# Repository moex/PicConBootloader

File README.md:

PicConBootloader
================

Primeras placas de Pic con Bootloader

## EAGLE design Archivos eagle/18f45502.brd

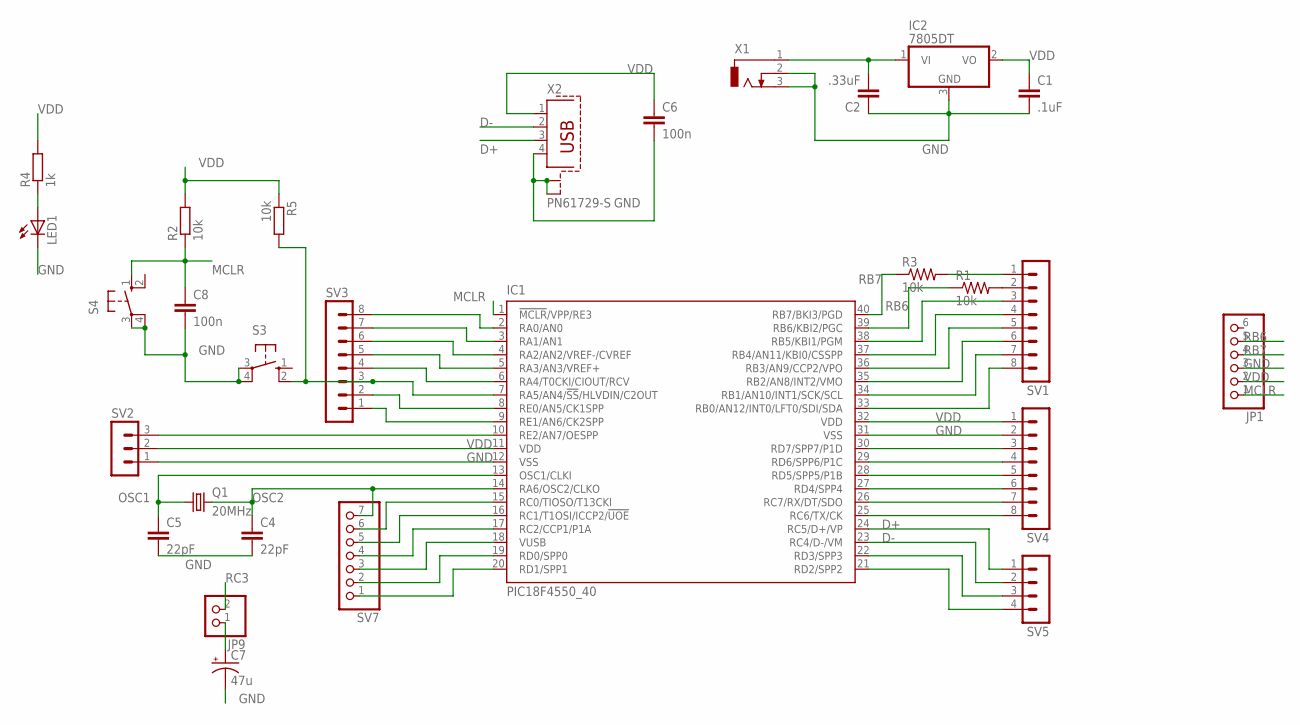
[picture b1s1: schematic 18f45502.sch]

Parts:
C1: .1uF; C0805K
C2: .33uF; C0805K
C4, C5: 22pF; C0805K
C6, C8: 100n; C0805K
C7: 47u; TT2D5L
IC1: PIC18F4550_40; DIL40
IC2: 7805DT; TO252
JP1: PINHD-1X6; 1X06
JP9: PINHD-1X2; 1X02
LED1: LED3MM
Q1: 20MHz; HC49/S
R1, R2, R3, R5: 10k; R0805
R4: 1k; R0805
S3, S4: 10-XX; B3F-10XX
SV1, SV3, SV4: MA08-1
SV2: MA03-1
SV5: MA04-1
SV7: PINHD-1X7; 1X07
X1: DCJ0202
X2: PN61729-S

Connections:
D+: IC1.24 (RC5/D+/VP), SV5.1, X2.3
D-: IC1.23 (RC4/D-/VM), SV5.2, X2.2
GND: C1.2, C2.1, C4.2, C5.2, C6.2, C7.-, C8.2, IC1.12 (VSS), IC1.31 (VSS), IC2.3 (GND), JP1.3, LED1.K (C), S3.3, S3.4 (P1), S4.3, S4.4 (P1), SV2.1, SV4.2, X1.2, X1.3, X2.4, X2.S1, X2.S2
MCLR: C8.1, IC1.1 (!MCLR!/VPP/RE3), JP1.1, R2.1, S4.1 (S)
unnamed: R3.2, SV1.1
unnamed: R1.2, SV1.2
unnamed: IC1.38 (RB5/KBI1/PGM), SV1.3
unnamed: IC1.37 (RB4/AN11/KBI0/CSSPP), SV1.4
unnamed: IC1.36 (RB3/AN9/CCP2/VPO), SV1.5
unnamed: IC1.35 (RB2/AN8/INT2/VMO), SV1.6
unnamed: IC1.34 (RB1/AN10/INT1/SCK/SCL), SV1.7
unnamed: IC1.33 (RB0/AN12/INT0/LFT0/SDI/SDA), SV1.8
unnamed: IC1.30 (RD7/SPP7/P1D), SV4.3
unnamed: IC1.29 (RD6/SPP6/P1C), SV4.4
unnamed: IC1.28 (RD5/SPP5/P1B), SV4.5
unnamed: IC1.27 (RD4/SPP4), SV4.6
unnamed: IC1.2 (RA0/AN0), SV3.8
unnamed: IC1.3 (RA1/AN1), SV3.7
unnamed: IC1.4 (RA2/AN2/VREF-/CVREF), SV3.6
unnamed: IC1.5 (RA3/AN3/VREF+), SV3.5
unnamed: IC1.6 (RA4/T0CKI/CIOUT/RCV), SV3.4
unnamed: IC1.7 (RA5/AN4/!SS!/HLVDIN/C2OUT), R5.2, S3.2 (S1), SV3.3
unnamed: IC1.10 (RE2/AN7/OESPP), SV2.3
unnamed: IC1.9 (RE1/AN6/CK2SPP), SV3.1
unnamed: IC1.8 (RE0/AN5/CK1SPP), SV3.2
unnamed: IC1.21 (RD2/SPP2), SV5.4
unnamed: IC1.22 (RD3/SPP3), SV5.3
unnamed: IC1.15 (RC0/TIOSO/T13CKI), SV7.6
unnamed: IC1.16 (RC1/T1OSI/ICCP2/!UOE), SV7.5
unnamed: IC1.17 (RC2/CCP1/P1A), SV7.4
unnamed: IC1.26 (RC7/RX/DT/SDO), SV4.7
unnamed: IC1.25 (RC6/TX/CK), SV4.8
unnamed: IC1.19 (RD0/SPP0), SV7.2
unnamed: IC1.20 (RD1/SPP1), SV7.1
unnamed: LED1.A, R4.1
unnamed: C2.2, IC2.1 (VI), X1.1
unnamed: C7.+, JP9.1
OSC1: C5.1, IC1.13 (OSC1/CLKI), Q1.1
OSC2: C4.1, IC1.14 (RA6/OSC2/CLKO), Q1.2, SV7.7
RB6: IC1.39 (RB6/KBI2/PGC), JP1.5, R1.1
RB7: IC1.40 (RB7/BKI3/PGD), JP1.4, R3.1
RC3: IC1.18 (VUSB), JP9.2, SV7.3
VDD: C1.1, C6.1, IC1.11 (VDD), IC1.32 (VDD), IC2.2 (VO), JP1.2, R2.2, R4.2, R5.1, SV2.2, SV4.1, X2.1

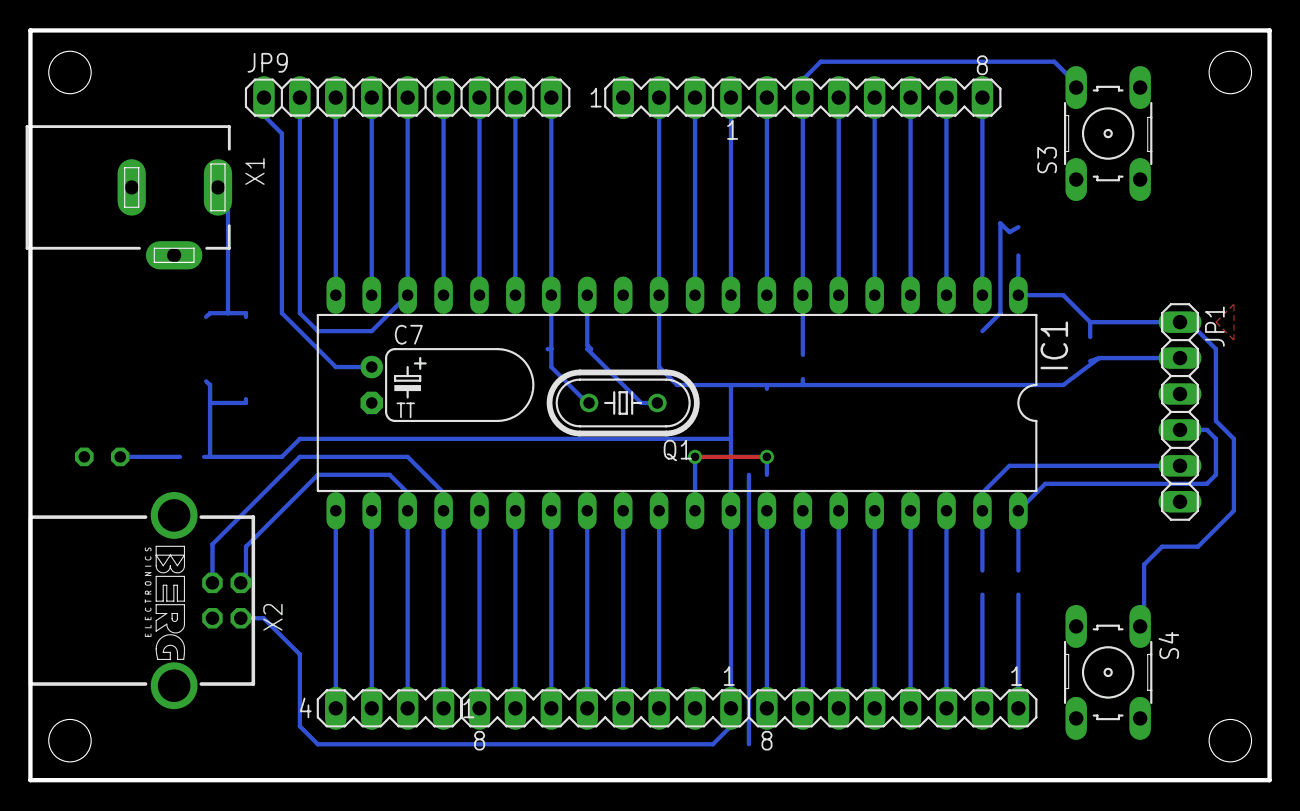
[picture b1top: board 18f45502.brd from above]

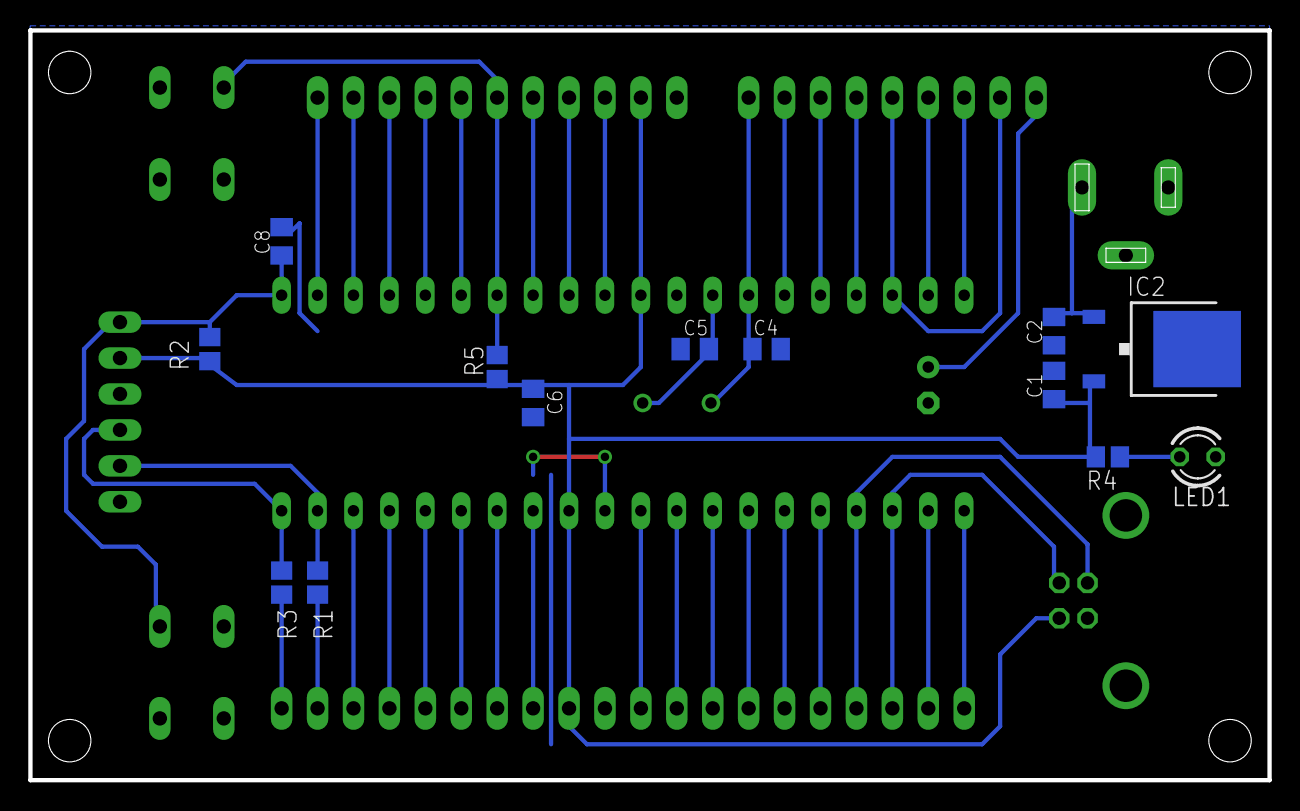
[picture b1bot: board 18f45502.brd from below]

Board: 2 copper layers, 87.6 x 53.0 mm, 28 parts (13 on the bottom side), 43 nets.

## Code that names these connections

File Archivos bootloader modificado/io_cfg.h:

/*********************************************************************
 *
 *                Microchip USB C18 Firmware 
 *
 *********************************************************************
 * FileName:        io_cfg.h
 * Dependencies:    See INCLUDES section below
 * Processor:       PIC18
 * Compiler:        C18 3.11+
 * Company:         Microchip Technology, Inc.
 *
 * Software License Agreement
 *
 * The software supplied herewith by Microchip Technology Incorporated
 * (the Company) for its PICmicro® Microcontroller is intended and
 * supplied to you, the Companys customer, for use solely and
 * exclusively on Microchip PICmicro Microcontroller products. The
 * software is owned by the Company and/or its supplier, and is
 * protected under applicable copyright laws. All rights are reserved.
 * Any use in violation of the foregoing restrictions may subject the
 * user to criminal sanctions under applicable laws, as well as to
 * civil liability for the breach of the terms and conditions of this
 * license.
 *
 * THIS SOFTWARE IS PROVIDED IN AN AS IS CONDITION. NO WARRANTIES,
 * WHETHER EXPRESS, IMPLIED OR STATUTORY, INCLUDING, BUT NOT LIMITED
 * TO, IMPLIED WARRANTIES OF MERCHANTABILITY AND FITNESS FOR A
 * PARTICULAR PURPOSE APPLY TO THIS SOFTWARE. THE COMPANY SHALL NOT,
 * IN ANY CIRCUMSTANCES, BE LIABLE FOR SPECIAL, INCIDENTAL OR
 * CONSEQUENTIAL DAMAGES, FOR ANY REASON WHATSOEVER.
 *
 * File Version  Date		Comment
 *~~~~~~~~~~~~~~~~~~~~~~~~~~~~~~~~~~~~~~~~~~~~~~~~~~~~~~~~~~~~~~~~~~~~
 * 1.0			 04/09/2008	Started from MCHPFSUSB v1.3 HID Mouse
 *							demo project.  Commented out items that
 *							are not particularly useful for the
 *							bootloader.
 ********************************************************************/

#ifndef IO_CFG_H
#define IO_CFG_H

/** I N C L U D E S *************************************************/
#include "usbcfg.h"

/** T R I S *********************************************************/
#define INPUT_PIN           1
#define OUTPUT_PIN          0

#if defined(PIC18F4550_PICDEM_FS_USB)
/** U S B ***********************************************************/
#define tris_usb_bus_sense  TRISAbits.TRISA1    // Input

#if defined(USE_USB_BUS_SENSE_IO)
#define usb_bus_sense       PORTAbits.RA1
#else
#define usb_bus_sense       1
#endif

#define tris_self_power     TRISAbits.TRISA2    // Input

#if defined(USE_SELF_POWER_SENSE_IO)
#define self_power          PORTAbits.RA2
#else
#define self_power          1
#endif

// External Transceiver Interface
/*#define tris_usb_vpo        TRISBbits.TRISB3    // Output
#define tris_usb_vmo        TRISBbits.TRISB2    // Output
#define tris_usb_rcv        TRISAbits.TRISA4    // Input
#define tris_usb_vp         TRISCbits.TRISC5    // Input
#define tris_usb_vm         TRISCbits.TRISC4    // Input
#define tris_usb_oe         TRISCbits.TRISC1    // Output

#define tris_usb_suspnd     TRISAbits.TRISA3    // Output*/

/** L E D ***********************************************************/
/*#define mInitAllLEDs()      LATD &= 0xF0; TRISD &= 0xF0;

#define mLED_1              LATDbits.LATD0
#define mLED_2              LATDbits.LATD1
#define mLED_3              LATDbits.LATD2
#define mLED_4              LATDbits.LATD3

#define mLED_1_On()         mLED_1 = 1;
#define mLED_2_On()         mLED_2 = 1;
#define mLED_3_On()         mLED_3 = 1;
#define mLED_4_On()         mLED_4 = 1;

#define mLED_1_Off()        mLED_1 = 0;
#define mLED_2_Off()        mLED_2 = 0;
#define mLED_3_Off()        mLED_3 = 0;
#define mLED_4_Off()        mLED_4 = 0;

#define mLED_1_Toggle()     mLED_1 = !mLED_1;
#define mLED_2_Toggle()     mLED_2 = !mLED_2;
#define mLED_3_Toggle()     mLED_3 = !mLED_3;
#define mLED_4_Toggle()     mLED_4 = !mLED_4;*/

/** S W I T C H *****************************************************/
#define mInitAllSwitches()  TRISAbits.TRISA5=1;
#define mInitSwitch2()      TRISAbits.TRISA5=1;
//#define mInitSwitch3()      TRISBbits.TRISB5=1;
#define sw2                 PORTAbits.RA5
//#define sw3                 PORTBbits.RB5

/** P O T ***********************************************************/
//#define mInitPOT()          TRISAbits.TRISA0=1;ADCON0=0x01;ADCON2=0x3C;

/** S P I : Chip Select Lines ***************************************/
//#define tris_cs_temp_sensor TRISBbits.TRISB2    // Output
//#define cs_temp_sensor      LATBbits.LATB2

//#define tris_cs_sdmmc       TRISBbits.TRISB3    // Output
//#define cs_sdmmc            LATBbits.LATB3

/** S D M M C *******************************************************/
//#define TRIS_CARD_DETECT    TRISBbits.TRISB4    // Input
//#define CARD_DETECT         PORTBbits.RB4

//#define TRIS_WRITE_DETECT   TRISAbits.TRISA4    // Input
//#define WRITE_DETECT        PORTAbits.RA4

/********************************************************************/
/********************************************************************/
/********************************************************************/



#elif defined(LOW_PIN_COUNT_USB_DEVELOPMENT_KIT)
	//Uncomment the below line(s) if the hardware supports it and
	//it is desireable to use one or both of the features.
	//#define USE_SELF_POWER_SENSE_IO	
	//#define USE_USB_BUS_SENSE_IO

    #define tris_usb_bus_sense  TRISAbits.TRISA1    // Input


	#if defined(USE_USB_BUS_SENSE_IO)
	#define usb_bus_sense       PORTAbits.RA1
	#else
	#define usb_bus_sense       1
	#endif
	
	#define tris_self_power     TRISAbits.TRISA2    // Input
	
	#if defined(USE_SELF_POWER_SENSE_IO)
	#define self_power          PORTAbits.RA2
	#else
	#define self_power          1
	#endif

    
    /** LED ************************************************************/
    /*#define mInitAllLEDs()      LATC &= 0xF0; TRISC &= 0xF0;
    
    #define mLED_1              LATCbits.LATC0
    #define mLED_2              LATCbits.LATC1
    #define mLED_3              LATCbits.LATC2
    #define mLED_4              LATCbits.LATC3
    
    #define mLED_1_On()         mLED_1 = 1;
    #define mLED_2_On()         mLED_2 = 1;
    #define mLED_3_On()         mLED_3 = 1;
    #define mLED_4_On()         mLED_4 = 1;
    
    #define mLED_1_Off()        mLED_1 = 0;
    #define mLED_2_Off()        mLED_2 = 0;
    #define mLED_3_Off()        mLED_3 = 0;
    #define mLED_4_Off()        mLED_4 = 0;
    
    #define mLED_1_Toggle()     mLED_1 = !mLED_1;
    #define mLED_2_Toggle()     mLED_2 = !mLED_2;
    #define mLED_3_Toggle()     mLED_3 = !mLED_3;
    #define mLED_4_Toggle()     mLED_4 = !mLED_4;*/
    
    /** SWITCH *********************************************************/
    #define mInitSwitch2()      //TRISAbits.TRISA3=1
        //only one switch available so double duty
    //#define mInitSwitch3()      //TRISAbits.TRISA3=1
    #define sw2                 PORTAbits.RA5
    //#define sw3                 PORTAbits.RA3
    #define mInitAllSwitches()  mInitSwitch2();
    
    /** POT ************************************************************/
    //#define mInitPOT()          {TRISBbits.TRISB4=1;ADCON0=0x29;ADCON1=0;ADCON2=0x3E;ADCON2bits.ADFM = 1;}





//Uncomment below if using the YOUR_BOARD hardware platform
//#elif defined(YOUR_BOARD)
//Add your hardware specific I/O pin mapping here

#else
    #error Not a supported board (yet), add I/O pin mapping in __FILE__, line __LINE__
#endif

#endif //IO_CFG_H

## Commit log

2014-12-28 :circus_tent: Added .gitattributes
2014-12-28 Primeros archivos
    Archivos básicos
2014-12-28 Archivos acomodados
2014-12-30 build alpha 1.1
2014-12-30 build alpha 1.2
    se soluciono una obstrucción física que impedia extraer el micro de su
    zócalo y se encontró una mayor área de disipación para el regulador
2014-12-30 build alpha 1.3
    se acomodaron los agujeros porque estaban tocando el borde de la placa y
    los pulsadores se re ubicaron de una forma simetrica
2014-12-30 build alpha 1.3.1
    modificaciones menores
2014-12-30 build alpha 1.4
    0402 por 0805
2014-12-30 Cambios la Silkscreen
2014-12-30 Agregué lista de componentes
2014-12-30 Correciones a la lista de componentes
2015-01-02 build alpha 1.4.1
    arregle el tema de la masa que quedaba separada, puse un puente que
    queda oculto debajo del micro
2015-01-07 build alpha 1.5.1
    se agrego una resistencia de pull up en el pulsador de bootloader (super
    importante)
2015-01-12 build 1.5.2
    se agregaron archivos para el bootloader
